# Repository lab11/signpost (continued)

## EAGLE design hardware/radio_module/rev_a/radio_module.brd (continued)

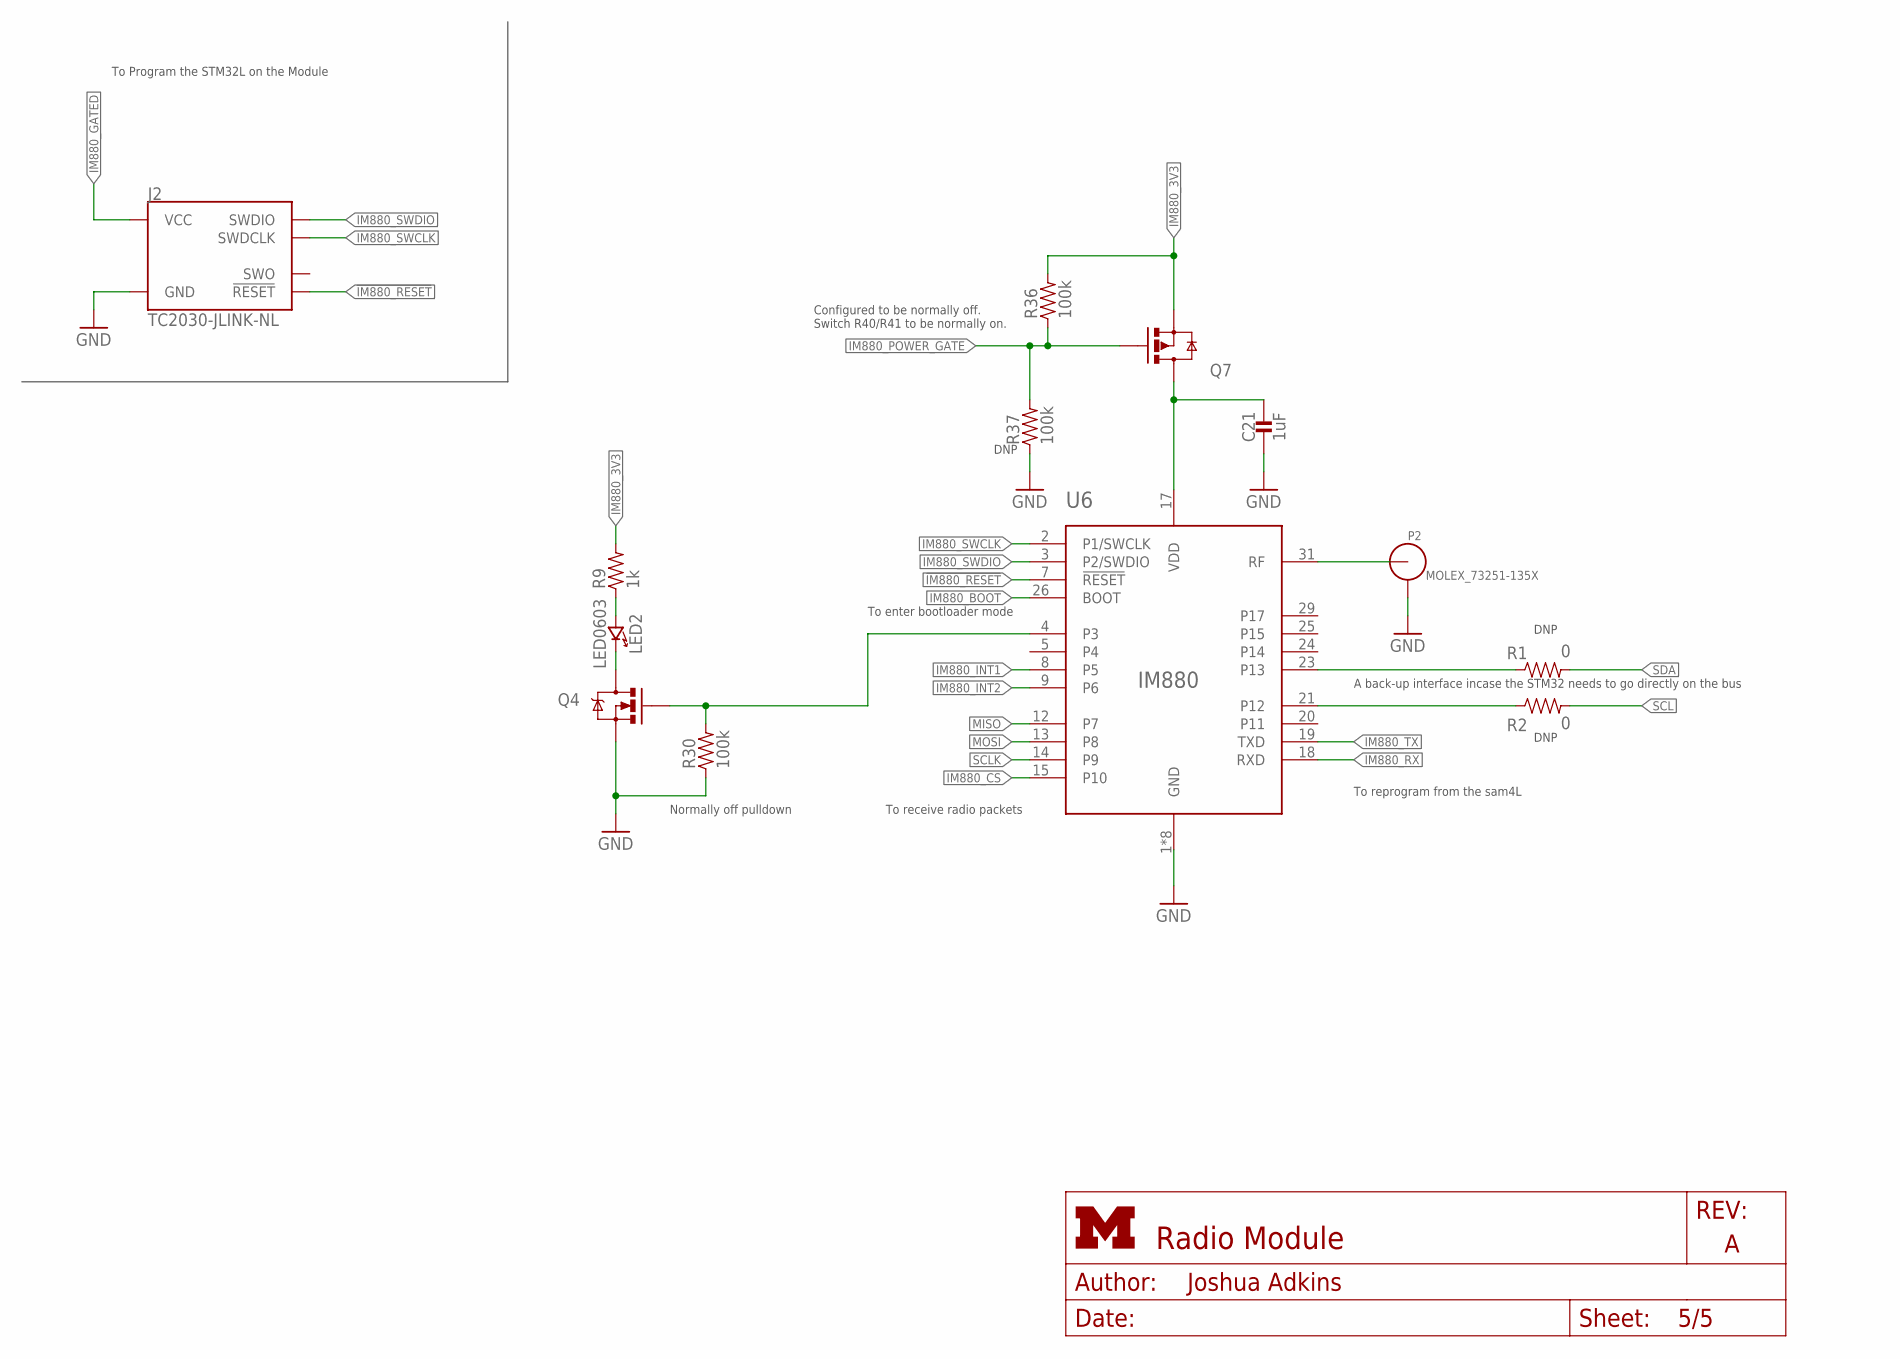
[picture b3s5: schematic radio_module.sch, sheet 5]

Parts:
C21: 1uF; 0402_CAP
J2: TC2030-JLINK-NL; TC2030-IDC-NL
LED2: LED0603; LED-0603
P2: MOLEX_73251-135X; SMA-J/PCB
Q4: MOSFET-NCHANNELXFDN-3; XFDFN-3
Q7: SI223DDS; SOT23-3
R1, R2: 0; 0402_RES
R9: 1k; 0402_RES
R30, R36, R37: 100k; 0402_RES
U6: IM880_MODULE

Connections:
!IM880_RESET: J2.3 (!RESET), U6.7 (!RESET); also elsewhere on the board
GND: C21.2, J2.5 (GND), P2.2, P2.3, P2.4, P2.5, Q4.S, R30.1, R37.1, U6.1 (GND), U6.6 (GND), U6.11 (GND), U6.16 (GND), U6.22 (GND), U6.27 (GND), U6.30 (GND), U6.32 (GND); also elsewhere on the board
IM880_3V3: Q7.2 (S), R9.2, R36.2; also elsewhere on the board
IM880_BOOT: U6.26 (BOOT); also elsewhere on the board
IM880_CS: U6.15 (P10); also elsewhere on the board
IM880_GATED: C21.1, J2.1 (VCC), Q7.3 (D), U6.17 (VDD)
IM880_INT1: U6.8 (P5); also elsewhere on the board
IM880_INT2: U6.9 (P6); also elsewhere on the board
IM880_NETWORK: Q4.G, R30.2, U6.4 (P3)
IM880_POWER_GATE: Q7.1 (G), R36.1, R37.2; also elsewhere on the board
IM880_RX: U6.18 (RXD); also elsewhere on the board
IM880_SWCLK: J2.4 (SWDCLK), U6.2 (P1/SWCLK)
IM880_SWDIO: J2.2 (SWDIO), U6.3 (P2/SWDIO)
IM880_TX: U6.19 (TXD); also elsewhere on the board
MISO: U6.12 (P7); also elsewhere on the board
MOSI: U6.13 (P8); also elsewhere on the board
unnamed: P2.1 (ANT), U6.31 (RF)
unnamed: R1.1, U6.23 (P13)
unnamed: R2.1, U6.21 (P12)
unnamed: LED2.A (ANODE), R9.1
unnamed: LED2.C (CATHODE), Q4.D
SCL: R2.2; also elsewhere on the board
SCLK: U6.14 (P9); also elsewhere on the board
SDA: R1.2; also elsewhere on the board

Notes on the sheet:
To Program the STM32L on the Module
To reprogram from the sam4L
To receive radio packets
A back-up interface incase the STM32 needs to go directly on the bus
To enter bootloader mode
DNP
Configured to be normally off. Switch R40/R41 to be normally on.
Normally off pulldown

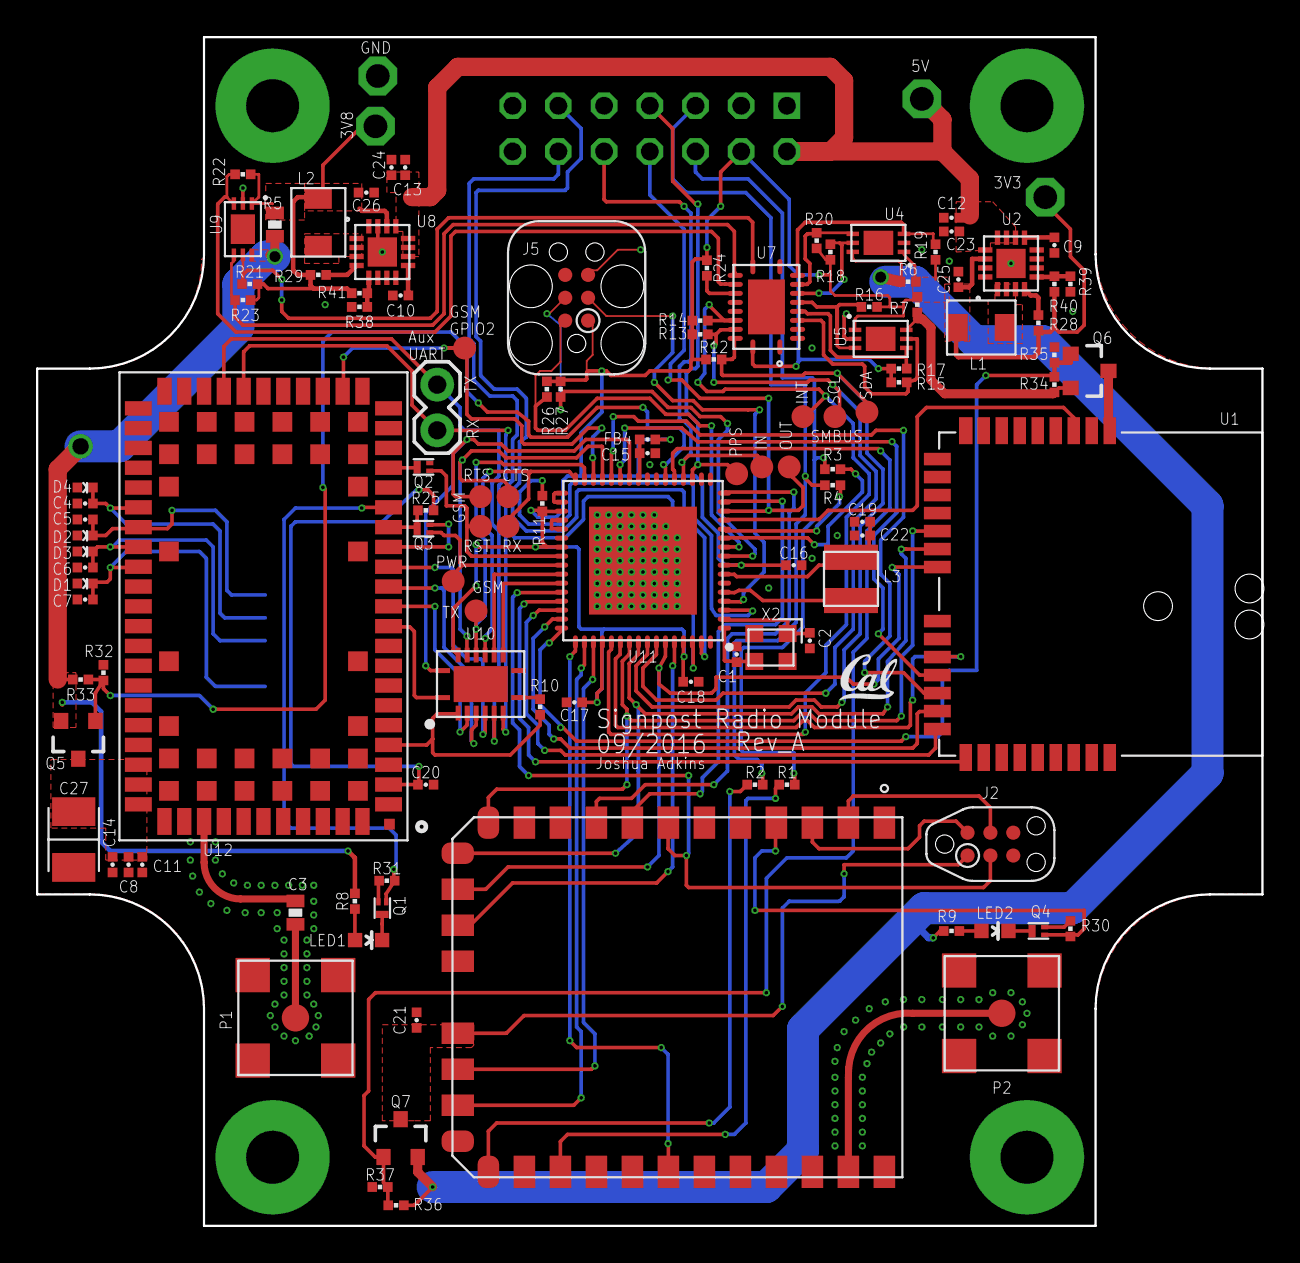
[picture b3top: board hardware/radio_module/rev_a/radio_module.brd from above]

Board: 4 copper layers, 68.1 x 66.0 mm, 122 parts (1 on the bottom side), 108 nets.

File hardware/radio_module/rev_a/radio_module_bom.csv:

# Bill of Materials
# Converted from radio_module_bom.xlsx
# Generated by bom_to_text.py

Part,Value,Device,Package,Description,DIGIKEY
C1,8pF,CAPACITOR0402_CAP,0402_CAP,0402 Capacitor,490-5867-1-ND
C2,8pF,CAPACITOR0402_CAP,0402_CAP,0402 Capacitor,490-5867-1-ND
C3,33pF,CAPACITOR0603_CAP,0603_CAP,0402 Capacitor,490-6241-1-ND
C4,47pF,CAPACITOR0402_CAP,0402_CAP,0402 Capacitor,491-6241-1-ND
C5,47pF,CAPACITOR0402_CAP,0402_CAP,0402 Capacitor,492-6241-1-ND
C6,47pF,CAPACITOR0402_CAP,0402_CAP,0402 Capacitor,493-6241-1-ND
C7,47pF,CAPACITOR0402_CAP,0402_CAP,0402 Capacitor,494-6241-1-ND
C8,56pF,CAPACITOR0402_CAP,0402_CAP,0402 Capacitor,490-1288-1-ND
C9,3.3nF,CAPACITOR0402_CAP,0402_CAP,0402 Capacitor,490-3248-1-ND
C10,3.3nF,CAPACITOR0402_CAP,0402_CAP,0402 Capacitor,491-3248-1-ND
C11,10nF,CAPACITOR0402_CAP,0402_CAP,0402 Capacitor,490-4516-1-ND
C12,0.1uF,CAPACITOR0402_CAP,0402_CAP,0402 Capacitor,490-6328-1-ND
C13,0.1uF,CAPACITOR0402_CAP,0402_CAP,0402 Capacitor,491-6328-1-ND
C14,100nF,CAPACITOR0402_CAP,0402_CAP,0402 Capacitor,492-6328-1-ND
C15,100nF,CAPACITOR0402_CAP,0402_CAP,0402 Capacitor,493-6328-1-ND
C16,100nF,CAPACITOR0402_CAP,0402_CAP,0402 Capacitor,494-6328-1-ND
C17,100nF,CAPACITOR0402_CAP,0402_CAP,0402 Capacitor,495-6328-1-ND
C18,100nF,CAPACITOR0402_CAP,0402_CAP,0402 Capacitor,496-6328-1-ND
C19,100nF,CAPACITOR0402_CAP,0402_CAP,0402 Capacitor,497-6328-1-ND
C20,100nF,CAPACITOR0402_CAP,0402_CAP,0402 Capacitor,498-6328-1-ND
C21,1uF,CAPACITOR0402_CAP,0402_CAP,0402 Capacitor,490-1320-1-ND
C22,4.7uF,CAPACITOR0402_CAP,0402_CAP,0402 Capacitor,490-5915-1-ND
C23,10uF,CAPACITOR0402_CAP,0402_CAP,0402 Capacitor,311-1729-1-ND
C24,10uF,CAPACITOR0402_CAP,0402_CAP,0402 Capacitor,312-1729-1-ND
C25,22uF,CAPACITOR0402_CAP,0402_CAP,0402 Capacitor,1276-6834-1-ND
C26,22uF,CAPACITOR0402_CAP,0402_CAP,0402 Capacitor,1277-6834-1-ND
C27,220uF,CAPACITOR1210_CAP,1210_CAP,0402 Capacitor,1276-3375-1-ND
D1,,DIODE_ZENER,0402_DIODE,,PESD0402-140CT-ND
D2,,DIODE_ZENER,0402_DIODE,,PESD0402-140CT-ND
D3,,DIODE_ZENER,0402_DIODE,,PESD0402-140CT-ND
D4,,DIODE_ZENER,0402_DIODE,,PESD0402-140CT-ND
FB4,1.5k,FERRITE_BEAD0402,0402_CAP,,490-5216-1-ND
J1,MODULE_GENERIC,MODULE_GENERIC,MODULE_GENERIC,Module header and PCB  guildes for signposts,S9170-ND
J4,NANO_SIM,NANO_SIM,WURTH_NANO_SIM,WURTH Nano SIM Connector,732-5954-1-ND
JP1,,M02PTH,1X02,Header 2,3M9447-ND
L1,2.2uH,INDUCTORIHL,IHL-1212BZ-11,A very specific inductor,541-1322-1-ND
L2,2.2uH,INDUCTORIHL,IHL-1212BZ-11,A very specific inductor,541-1322-1-ND
L3,22uH,LHQ3NP,1212,LHQ3NP Inductor,490-5350-1-ND
LED1,LED0603,LED0603,LED-0603,LED,511-1578-1-ND
LED2,LED0603,LED0603,LED-0603,LED,512-1578-1-ND
P1,MOLEX_73251-135X,MOLEX_73251-135X,SMA-J/PCB,SMA JACK SMT 50 OHM,WM9357-ND
P2,MOLEX_73251-135X,MOLEX_73251-135X,SMA-J/PCB,SMA JACK SMT 50 OHM,WM9357-ND
Q1,MOSFET-NCHANNELXFDN-3,MOSFET-NCHANNELXFDN-3,XFDFN-3,Generic NMOS footprint,DMN2400UFB4-7DICT-ND
Q2,MOSFET-NCHANNELXFDN-3,MOSFET-NCHANNELXFDN-3,XFDFN-3,Generic NMOS footprint,DMN2400UFB4-7DICT-ND
Q3,MOSFET-NCHANNELXFDN-3,MOSFET-NCHANNELXFDN-3,XFDFN-3,Generic NMOS footprint,DMN2400UFB4-7DICT-ND
Q4,MOSFET-NCHANNELXFDN-3,MOSFET-NCHANNELXFDN-3,XFDFN-3,Generic NMOS footprint,DMN2400UFB4-7DICT-ND
Q5,SI223DDS,SI223DDS,SOT23-3,6A SOT-23 P Fet,SI2333DDS-T1-GE3CT-ND
Q6,SI223DDS,SI223DDS,SOT23-3,6A SOT-23 P Fet,SI2333DDS-T1-GE3CT-ND
Q7,SI223DDS,SI223DDS,SOT23-3,6A SOT-23 P Fet,SI2333DDS-T1-GE3CT-ND
R1,0,RESISTOR0402_RES,0402_RES,Resistor,311-0.0JRCT-ND
R2,0,RESISTOR0402_RES,0402_RES,Resistor,312-0.0JRCT-ND
R3,0,RESISTOR0402_RES,0402_RES,Resistor,313-0.0JRCT-ND
R4,0,RESISTOR0402_RES,0402_RES,Resistor,314-0.0JRCT-ND
R5,0.015,RESISTOR0603_RES,0603-RES,Resistor,408-1406-1-ND
R6,0.43,RESISTOR0402_RES,0402_RES,Resistor,P.43AKCT-ND
R7,3.32,RESISTOR0402_RES,0402_RES,Resistor,541-3.32LLCT-ND
R8,1k,RESISTOR0402_RES,0402_RES,Resistor,311-1.0KJRCT-ND
R9,1k,RESISTOR0402_RES,0402_RES,Resistor,312-1.0KJRCT-ND
R10,10k,RESISTOR0402_RES,0402_RES,Resistor,311-10KJRCT-ND
R11,10k,RESISTOR0402_RES,0402_RES,Resistor,312-10KJRCT-ND
R12,10k,RESISTOR0402_RES,0402_RES,Resistor,313-10KJRCT-ND
R13,10k,RESISTOR0402_RES,0402_RES,Resistor,314-10KJRCT-ND
R14,10k,RESISTOR0402_RES,0402_RES,Resistor,315-10KJRCT-ND
R15,10k,RESISTOR0402_RES,0402_RES,Resistor,316-10KJRCT-ND
R16,10k,RESISTOR0402_RES,0402_RES,Resistor,317-10KJRCT-ND
R17,10k,RESISTOR0402_RES,0402_RES,Resistor,318-10KJRCT-ND
R18,10k,RESISTOR0402_RES,0402_RES,Resistor,319-10KJRCT-ND
R19,10k,RESISTOR0402_RES,0402_RES,Resistor,320-10KJRCT-ND
R20,10k,RESISTOR0402_RES,0402_RES,Resistor,321-10KJRCT-ND
R21,10k,RESISTOR0402_RES,0402_RES,Resistor,322-10KJRCT-ND
R22,10k,RESISTOR0402_RES,0402_RES,Resistor,323-10KJRCT-ND
R23,10k,RESISTOR0402_RES,0402_RES,Resistor,324-10KJRCT-ND
R24,10k,RESISTOR0402_RES,0402_RES,Resistor,325-10KJRCT-ND
R25,100k,RESISTOR0402_RES,0402_RES,Resistor,311-100KLRCT-ND
R26,100k,RESISTOR0402_RES,0402_RES,Resistor,312-100KLRCT-ND
R27,100k,RESISTOR0402_RES,0402_RES,Resistor,313-100KLRCT-ND
R28,100k,RESISTOR0402_RES,0402_RES,Resistor,314-100KLRCT-ND
R29,100k,RESISTOR0402_RES,0402_RES,Resistor,315-100KLRCT-ND
R30,100k,RESISTOR0402_RES,0402_RES,Resistor,316-100KLRCT-ND
R31,100k,RESISTOR0402_RES,0402_RES,Resistor,317-100KLRCT-ND
R32,100k,RESISTOR0402_RES,0402_RES,Resistor,318-100KLRCT-ND
R33,100k,RESISTOR0402_RES,0402_RES,Resistor,319-100KLRCT-ND
R34,100k,RESISTOR0402_RES,0402_RES,Resistor,320-100KLRCT-ND
R35,100k,RESISTOR0402_RES,0402_RES,Resistor,321-100KLRCT-ND
R36,100k,RESISTOR0402_RES,0402_RES,Resistor,322-100KLRCT-ND
R37,100k,RESISTOR0402_RES,0402_RES,Resistor,323-100KLRCT-ND
R38,200k,RESISTOR0402_RES,0402_RES,Resistor,P200KLCT-ND
R39,240k,RESISTOR0402_RES,0402_RES,Resistor,YAG3291CT-ND
R40,750k,RESISTOR0402_RES,0402_RES,Resistor,YAG3228CT-ND
R41,750k,RESISTOR0402_RES,0402_RES,Resistor,YAG3228CT-ND
U1,NUCLEUM,NUCLEUM,NUCLEUM,Nucleum sensorboard prototyping module.,
U2,TLV62130,TLV62130,TQFN-16/3MM,"High Efficient 3A switching step-down regulator. 1V-5V out, 4V-17V in.",296-35978-1-ND
U4,LTC2941,LTC2941,DFN-6-2MMX3MM,I2C Battery Gas Gauge,LTC2941IDCB#TRMPBFCT-ND
U5,LTC2941,LTC2941,DFN-6-2MMX3MM,I2C Battery Gas Gauge,LTC2941IDCB#TRMPBFCT-ND
U6,IM880_MODULE,IM880_MODULE,IM880_MODULE,Lora Radio module by IMST,
U7,PCA9544AQFN-N20,PCA9544AQFN-N20,QFN-N20,1-4 I2C/SMBUS Multiplexer with interrupt for power supply coulomb counters,296-20960-1-ND
U8,TLV62130,TLV62130,TQFN-16/3MM,"High Efficient 3A switching step-down regulator. 1V-5V out, 4V-17V in.",296-35978-1-ND
U9,LTC2941,LTC2941,DFN-6-2MMX3MM,I2C Battery Gas Gauge,LTC2941IDCB#TRMPBFCT-ND
U10,TXB0106,TXB0106,R-PVQFN-N16,6 channel level translator,296-23868-2-ND
U11,SAM4LC8BA,SAM4LC8BA,QFN-64-9MM,SAM4L Microcontroller. 64QFN Package. 512 Flash.,ATSAM4LC8BA-MURDKR-ND
U12,UBLOX_SARA_G350,UBLOX_SARA_G350,UBLOX_SARA_G3,Sara G350 2.5G Radio Module,
X2,16 MHz,FH1600015,FHXXX,Pericom Type FH 16 MHz 2.5 x 2.0 mm,FH1600015CT-ND

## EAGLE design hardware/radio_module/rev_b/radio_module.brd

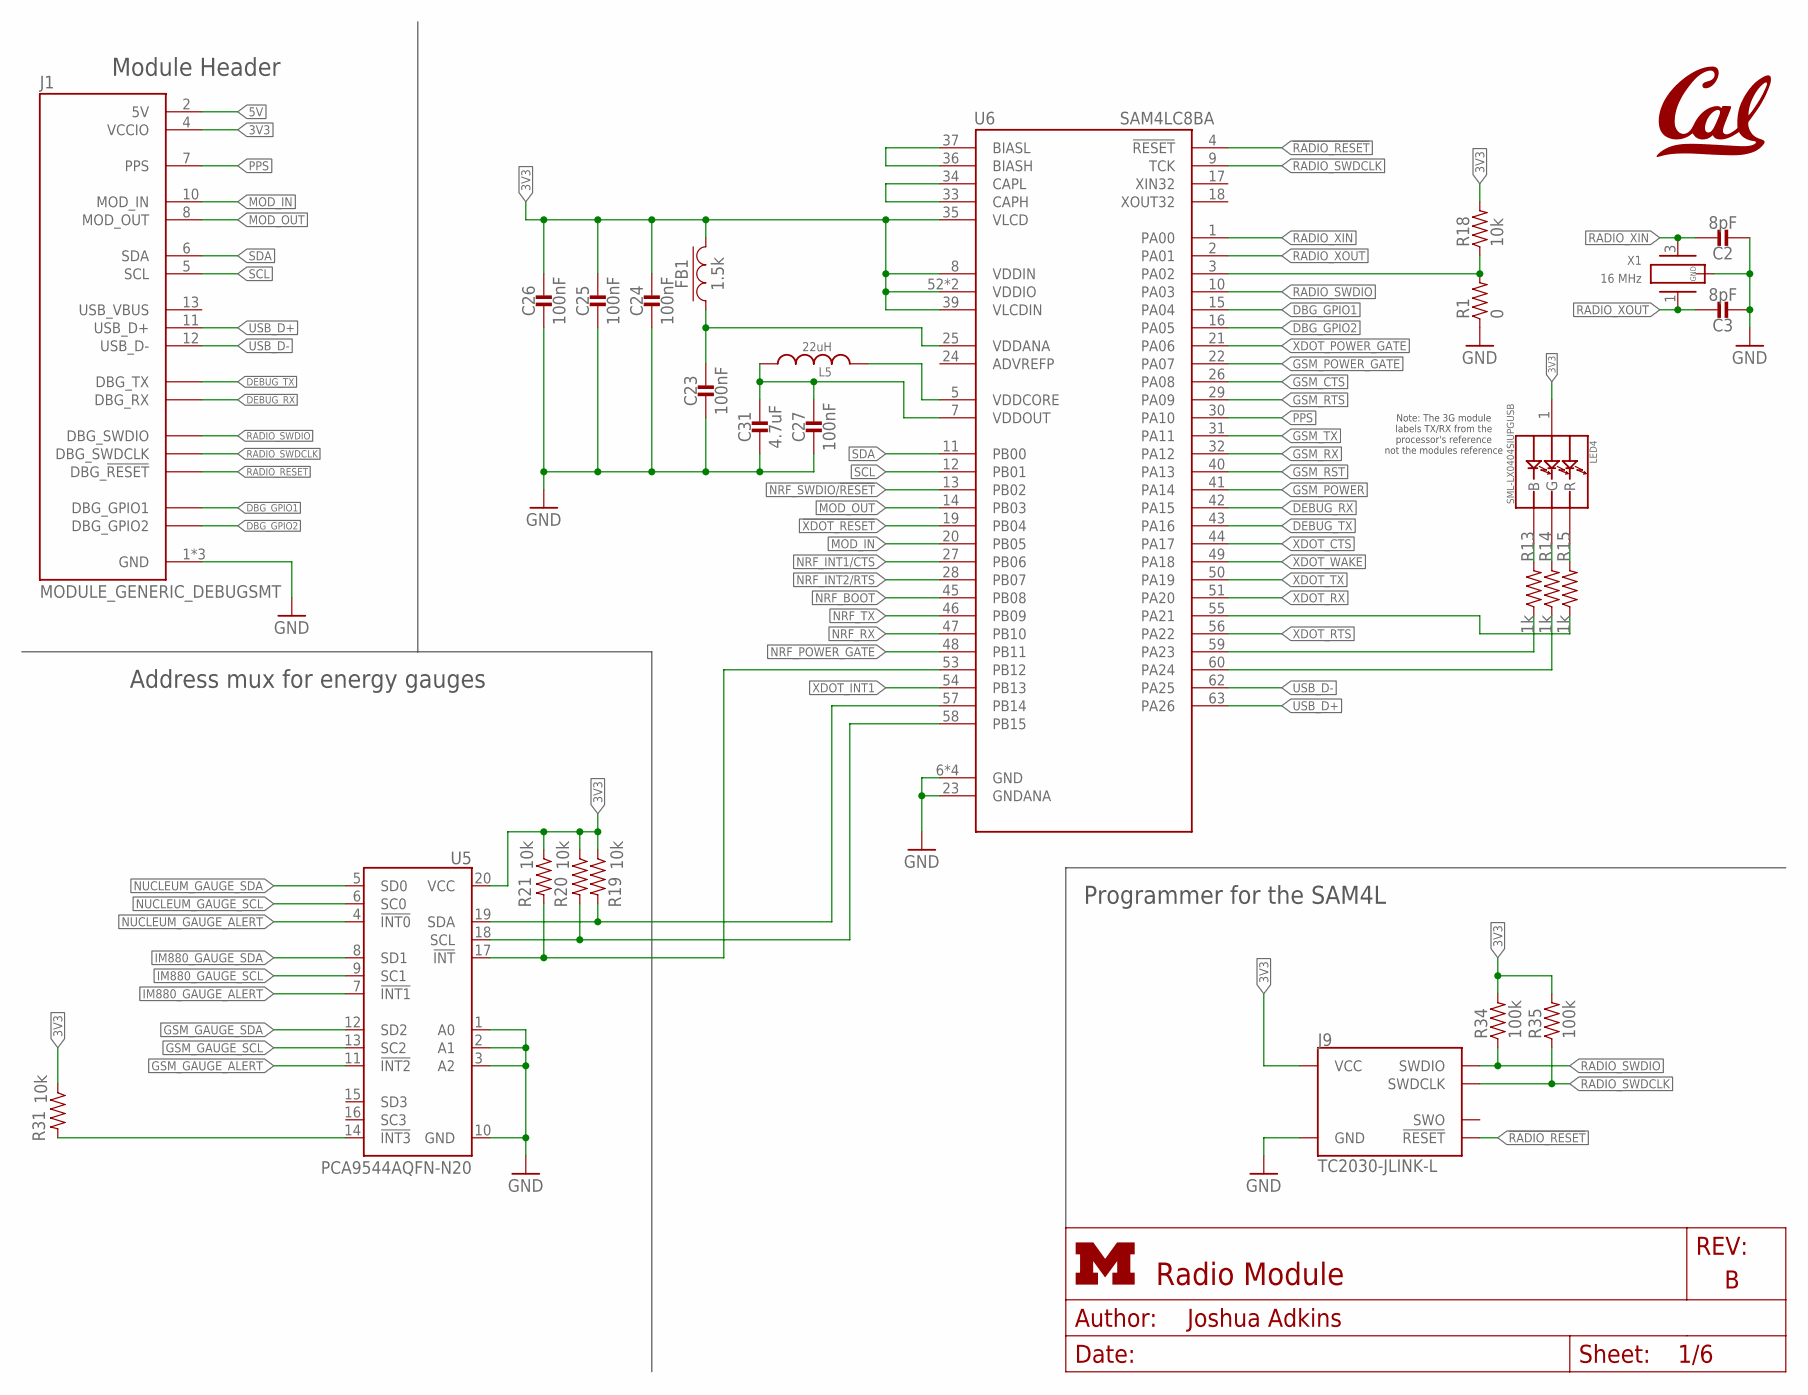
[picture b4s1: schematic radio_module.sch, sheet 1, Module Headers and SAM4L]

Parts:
C2, C3: 8pF; 0402_CAP; DIGIKEY 490-8230-1-ND
C23, C24, C25, C26, C27: 100nF; 0402_CAP; DIGIKEY 490-10777-1-ND
C31: 4.7uF; 0402_CAP; DIGIKEY 490-13252-1-ND
FB1: 1.5k; 0402_CAP; DIGIKEY 490-5216-1-ND
J1: MODULE_GENERIC_DEBUGSMT; MODULE_GENERIC_DEBUG_SMT
J9: TC2030-JLINK-L; TC2030-IDC
L5: 22uH; 1212
LED4: SML-LX0404SIUPGUSB; 1MM_SQ_4PAD
R1: 0; 0402_RES; DIGIKEY 311-0.0JRCT-ND
R13, R14, R15: 1k; 0402_RES; DIGIKEY 311-1.0KJRCT-ND
R18, R19, R20, R21, R31: 10k; 0402_RES; DIGIKEY 311-10KJRCT-ND
R34, R35: 100k; 0402_RES; DIGIKEY 311-100KLRCT-ND
U5: PCA9544AQFN-N20; QFN-N20
U6: SAM4LC8BA; QFN-64-9MM; DIGIKEY ATSAM4LC8BA-MU
U$1: UCB_CAL100MIL; UCB_CAL_100MIL
X1: 16 MHz; FHXXX

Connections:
3V3: C24.1, C25.1, C26.1, FB1.2, J1.4 (VCCIO), J9.1 (VCC), LED4.1 (VDD), R18.2, R19.1, R20.1, R21.1, R31.1, R34.2, R35.2, U5.20 (VCC), U6.8 (VDDIN), U6.35 (VLCD), U6.39 (VLCDIN), U6.52 (VDDIO), U6.61 (VDDIO); also elsewhere on the board
5V: J1.2 (5V); also elsewhere on the board
!RADIO_RESET: J1.20 (DBG_!RESET), J9.3 (!RESET), U6.4 (!RESET)
!XDOT_RESET: U6.19 (PB04); also elsewhere on the board
CONTROLLER_BUCK/LDO_N: R1.2, R18.1, U6.3 (PA02)
DBG_GPIO1: J1.16 (DBG_GPIO1), U6.15 (PA04)
DBG_GPIO2: J1.19 (DBG_GPIO2), U6.16 (PA05)
DEBUG_RX: J1.18 (DBG_RX), U6.42 (PA15)
DEBUG_TX: J1.17 (DBG_TX), U6.43 (PA16)
GND: C2.2, C3.2, C23.2, C24.2, C25.2, C26.2, C27.2, C31.2, J1.1 (GND), J1.14 (GND), J1.15 (GND), J9.5 (GND), R1.1, U5.1 (A0), U5.2 (A1), U5.3 (A2), U5.10 (GND), U6.6 (GND), U6.23 (GNDANA), U6.38 (GND), U6.64 (GND), U6.GND, X1.2 (GND), X1.4 (GND); also elsewhere on the board
GSM_CTS: U6.26 (PA08); also elsewhere on the board
GSM_GAUGE_ALERT: U5.11 (!INT2); also elsewhere on the board
GSM_GAUGE_SCL: U5.13 (SC2); also elsewhere on the board
GSM_GAUGE_SDA: U5.12 (SD2); also elsewhere on the board
GSM_POWER: U6.41 (PA14); also elsewhere on the board
GSM_POWER_GATE: U6.22 (PA07); also elsewhere on the board
GSM_RST: U6.40 (PA13); also elsewhere on the board
GSM_RTS: U6.29 (PA09); also elsewhere on the board
GSM_RX: U6.32 (PA12); also elsewhere on the board
GSM_TX: U6.31 (PA11); also elsewhere on the board
IM880_GAUGE_ALERT: U5.7 (!INT1); also elsewhere on the board
IM880_GAUGE_SCL: U5.9 (SC1); also elsewhere on the board
IM880_GAUGE_SDA: U5.8 (SD1); also elsewhere on the board
MOD_IN: J1.10 (MOD_IN), U6.20 (PB05)
MOD_OUT: J1.8 (MOD_OUT), U6.14 (PB03)
unnamed: R21.2, U5.17 (!INT), U6.53 (PB12)
unnamed: R31.2, U5.14 (!INT3)
unnamed: R13.1, U6.59 (PA23)
unnamed: LED4.3 (B), R13.2
unnamed: LED4.4 (G), R14.2
unnamed: LED4.2 (R), R15.2
unnamed: R14.1, U6.60 (PA24)
unnamed: R15.1, U6.55 (PA21)
unnamed: C23.1, FB1.1, U6.25 (VDDANA)
unnamed: C27.1, C31.1, L5.P$1 (1), U6.7 (VDDOUT)
unnamed: L5.P$2 (2), U6.5 (VDDCORE)
unnamed: U6.36 (BIASH), U6.37 (BIASL)
unnamed: U6.33 (CAPH), U6.34 (CAPL)
NRF_BOOT: U6.45 (PB08); also elsewhere on the board
NRF_INT1/CTS: U6.27 (PB06); also elsewhere on the board
NRF_INT2/RTS: U6.28 (PB07); also elsewhere on the board
NRF_POWER_GATE: U6.48 (PB11); also elsewhere on the board
NRF_RX: U6.47 (PB10); also elsewhere on the board
NRF_SWDIO/!RESET: U6.13 (PB02); also elsewhere on the board
NRF_TX: U6.46 (PB09); also elsewhere on the board
NUCLEUM_GAUGE_ALERT: U5.4 (!INT0); also elsewhere on the board
NUCLEUM_GAUGE_SCL: U5.6 (SC0); also elsewhere on the board
NUCLEUM_GAUGE_SDA: U5.5 (SD0); also elsewhere on the board
PPS: J1.7 (PPS), U6.30 (PA10)
RADIO_SWDCLK: J1.21 (DBG_SWDCLK), J9.4 (SWDCLK), R35.1, U6.9 (TCK)
RADIO_SWDIO: J1.22 (DBG_SWDIO), J9.2 (SWDIO), R34.1, U6.10 (PA03)
RADIO_XIN: C2.1, U6.1 (PA00), X1.3 (2)
RADIO_XOUT: C3.1, U6.2 (PA01), X1.1
SCL: J1.5 (SCL), U6.12 (PB01)
SCL_INTERNAL: R20.2, U5.18 (SCL), U6.58 (PB15)
SDA: J1.6 (SDA), U6.11 (PB00)
SDA_INTERNAL: R19.2, U5.19 (SDA), U6.57 (PB14)
USB_D+: J1.11 (USB_D+), U6.63 (PA26)
USB_D-: J1.12 (USB_D-), U6.62 (PA25)
XDOT_CTS: U6.44 (PA17); also elsewhere on the board
XDOT_INT1: U6.54 (PB13); also elsewhere on the board
XDOT_POWER_GATE: U6.21 (PA06); also elsewhere on the board
XDOT_RTS: U6.56 (PA22); also elsewhere on the board
XDOT_RX: U6.51 (PA20); also elsewhere on the board
XDOT_TX: U6.50 (PA19); also elsewhere on the board
XDOT_WAKE: U6.49 (PA18); also elsewhere on the board

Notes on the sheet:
Module Header
Address mux for energy gauges
Programmer for the SAM4L
Note: The 3G module labels TX/RX from the processor's reference not the modules reference

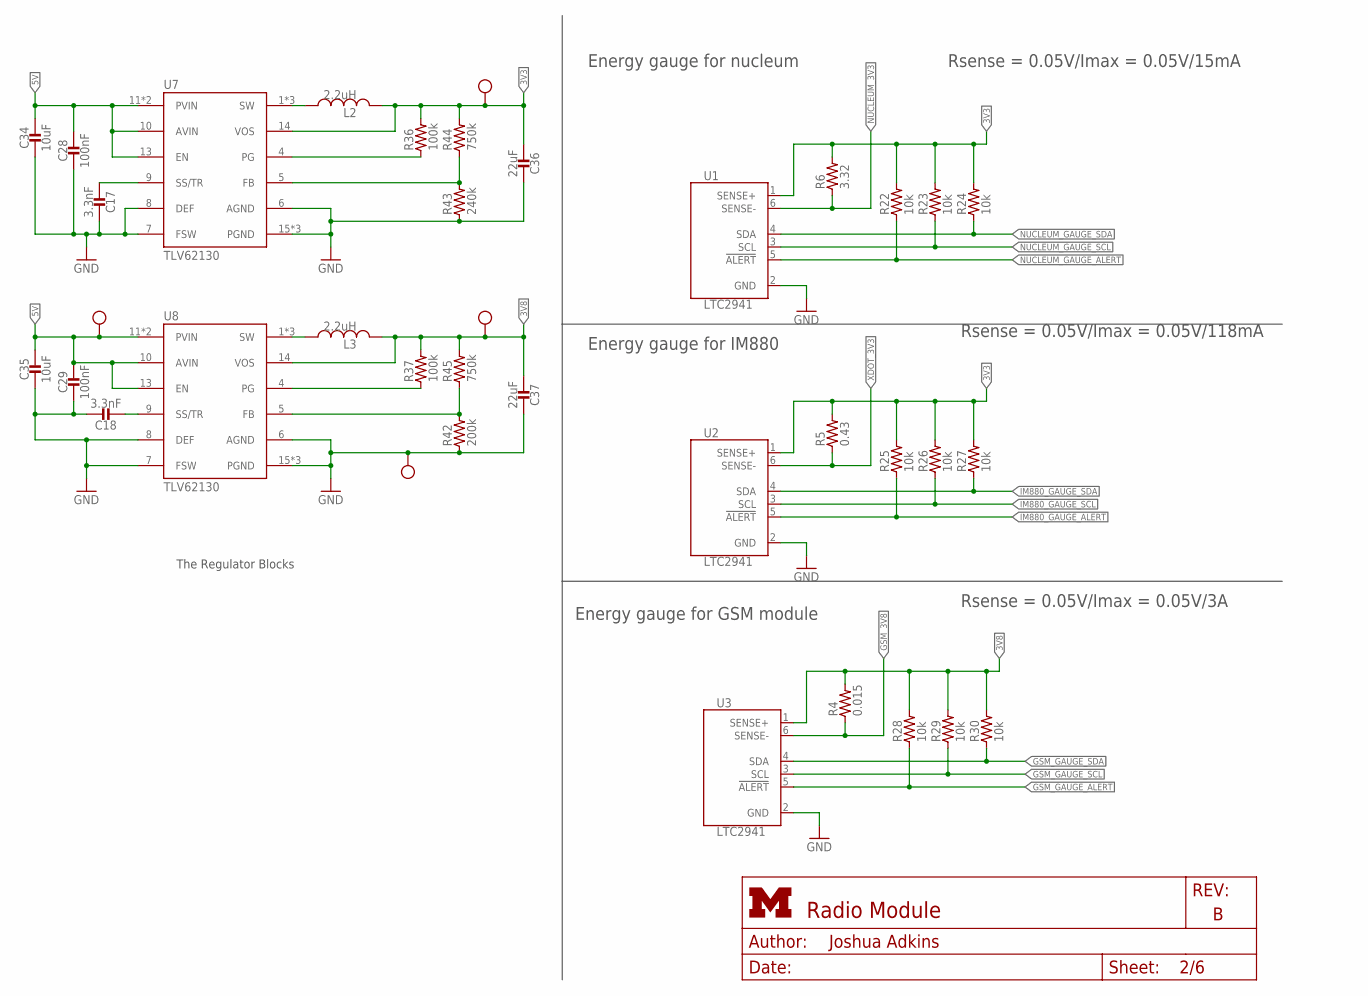
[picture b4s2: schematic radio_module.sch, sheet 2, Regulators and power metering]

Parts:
C17, C18: 3.3nF; 0402_CAP; DIGIKEY 490-3248-1-ND
C28, C29: 100nF; 0402_CAP; DIGIKEY 490-10777-1-ND
C34, C35: 10uF; 0402_CAP; DIGIKEY 490-13233-1-ND
C36, C37: 22uF; 0402_CAP; DIGIKEY 1276-6834-1-ND
L2, L3: 2.2uH; IHL-1212BZ-11
R4: 0.015; 0603-RES; DIGIKEY 408-1406-1-ND
R5: 0.43; 0402_RES; DIGIKEY P.43AKCT-ND
R6: 3.32; 0402_RES; DIGIKEY 541-3.32LLCT-ND
R22, R23, R24, R25, R26, R27, R28, R29, R30: 10k; 0402_RES; DIGIKEY 311-10KJRCT-ND
R36, R37: 100k; 0402_RES; DIGIKEY 311-100KLRCT-ND
R42: 200k; 0402_RES; DIGIKEY P200KLCT-ND
R43: 240k; 0402_RES; DIGIKEY YAG3291CT-ND
R44, R45: 750k; 0402_RES; DIGIKEY YAG3228CT-ND
TP1, TP2, TP3, TP4: TEST_POINT_0.040IN; TESTPOINT_0.040IN
U1, U2, U3: LTC2941; DFN-6-2MMX3MM
U7, U8: TLV62130; TQFN-16/3MM

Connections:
3V3: C36.2, L2.P$2 (2), R5.2, R6.2, R22.2, R23.2, R24.2, R25.2, R26.2, R27.2, R36.2, R44.2, TP1.TESTPOINT, U1.1 (SENSE+), U2.1 (SENSE+), U7.14 (VOS); also elsewhere on the board
3V8: C37.2, L3.P$2 (2), R4.2, R28.2, R29.2, R30.2, R37.2, R45.2, TP2.TESTPOINT, U3.1 (SENSE+), U8.14 (VOS)
3V8SWOUT: L3.P$1 (1), U8.1 (SW), U8.2 (SW), U8.3 (SW)
3VSWOUT: L2.P$1 (1), U7.1 (SW), U7.2 (SW), U7.3 (SW)
5V: C28.1, C29.1, C34.1, C35.1, TP4.TESTPOINT, U7.10 (AVIN), U7.11 (PVIN), U7.12 (PVIN), U7.13 (EN), U8.10 (AVIN), U8.11 (PVIN), U8.12 (PVIN), U8.13 (EN); also elsewhere on the board
GND: C17.1, C18.1, C28.2, C29.2, C34.2, C35.2, C36.1, C37.1, R42.1, R43.1, TP3.TESTPOINT, U1.2 (GND), U2.2 (GND), U3.2 (GND), U7.6 (AGND), U7.7 (FSW), U7.8 (DEF), U7.15 (PGND), U7.16 (PGND), U7.GND, U8.6 (AGND), U8.7 (FSW), U8.8 (DEF), U8.15 (PGND), U8.16 (PGND), U8.GND; also elsewhere on the board
GSM_3V8: R4.1, U3.6 (SENSE-); also elsewhere on the board
GSM_GAUGE_ALERT: R28.1, U3.5 (!ALERT); also elsewhere on the board
GSM_GAUGE_SCL: R29.1, U3.3 (SCL); also elsewhere on the board
GSM_GAUGE_SDA: R30.1, U3.4 (SDA); also elsewhere on the board
IM880_GAUGE_ALERT: R25.1, U2.5 (!ALERT); also elsewhere on the board
IM880_GAUGE_SCL: R26.1, U2.3 (SCL); also elsewhere on the board
IM880_GAUGE_SDA: R27.1, U2.4 (SDA); also elsewhere on the board
unnamed: C17.2, U7.9 (SS/TR)
unnamed: R36.1, U7.4 (PG)
unnamed: R43.2, R44.1, U7.5 (FB)
unnamed: C18.2, U8.9 (SS/TR)
unnamed: R37.1, U8.4 (PG)
unnamed: R42.2, R45.1, U8.5 (FB)
NUCLEUM_3V3: R6.1, U1.6 (SENSE-); also elsewhere on the board
NUCLEUM_GAUGE_ALERT: R22.1, U1.5 (!ALERT); also elsewhere on the board
NUCLEUM_GAUGE_SCL: R23.1, U1.3 (SCL); also elsewhere on the board
NUCLEUM_GAUGE_SDA: R24.1, U1.4 (SDA); also elsewhere on the board
XDOT_3V3: R5.1, U2.6 (SENSE-); also elsewhere on the board

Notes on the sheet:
The Regulator Blocks
Energy gauge for nucleum
Energy gauge for IM880
Energy gauge for GSM module
Rsense = 0.05V/Imax = 0.05V/15mA
Rsense = 0.05V/Imax = 0.05V/118mA
Rsense = 0.05V/Imax = 0.05V/3A

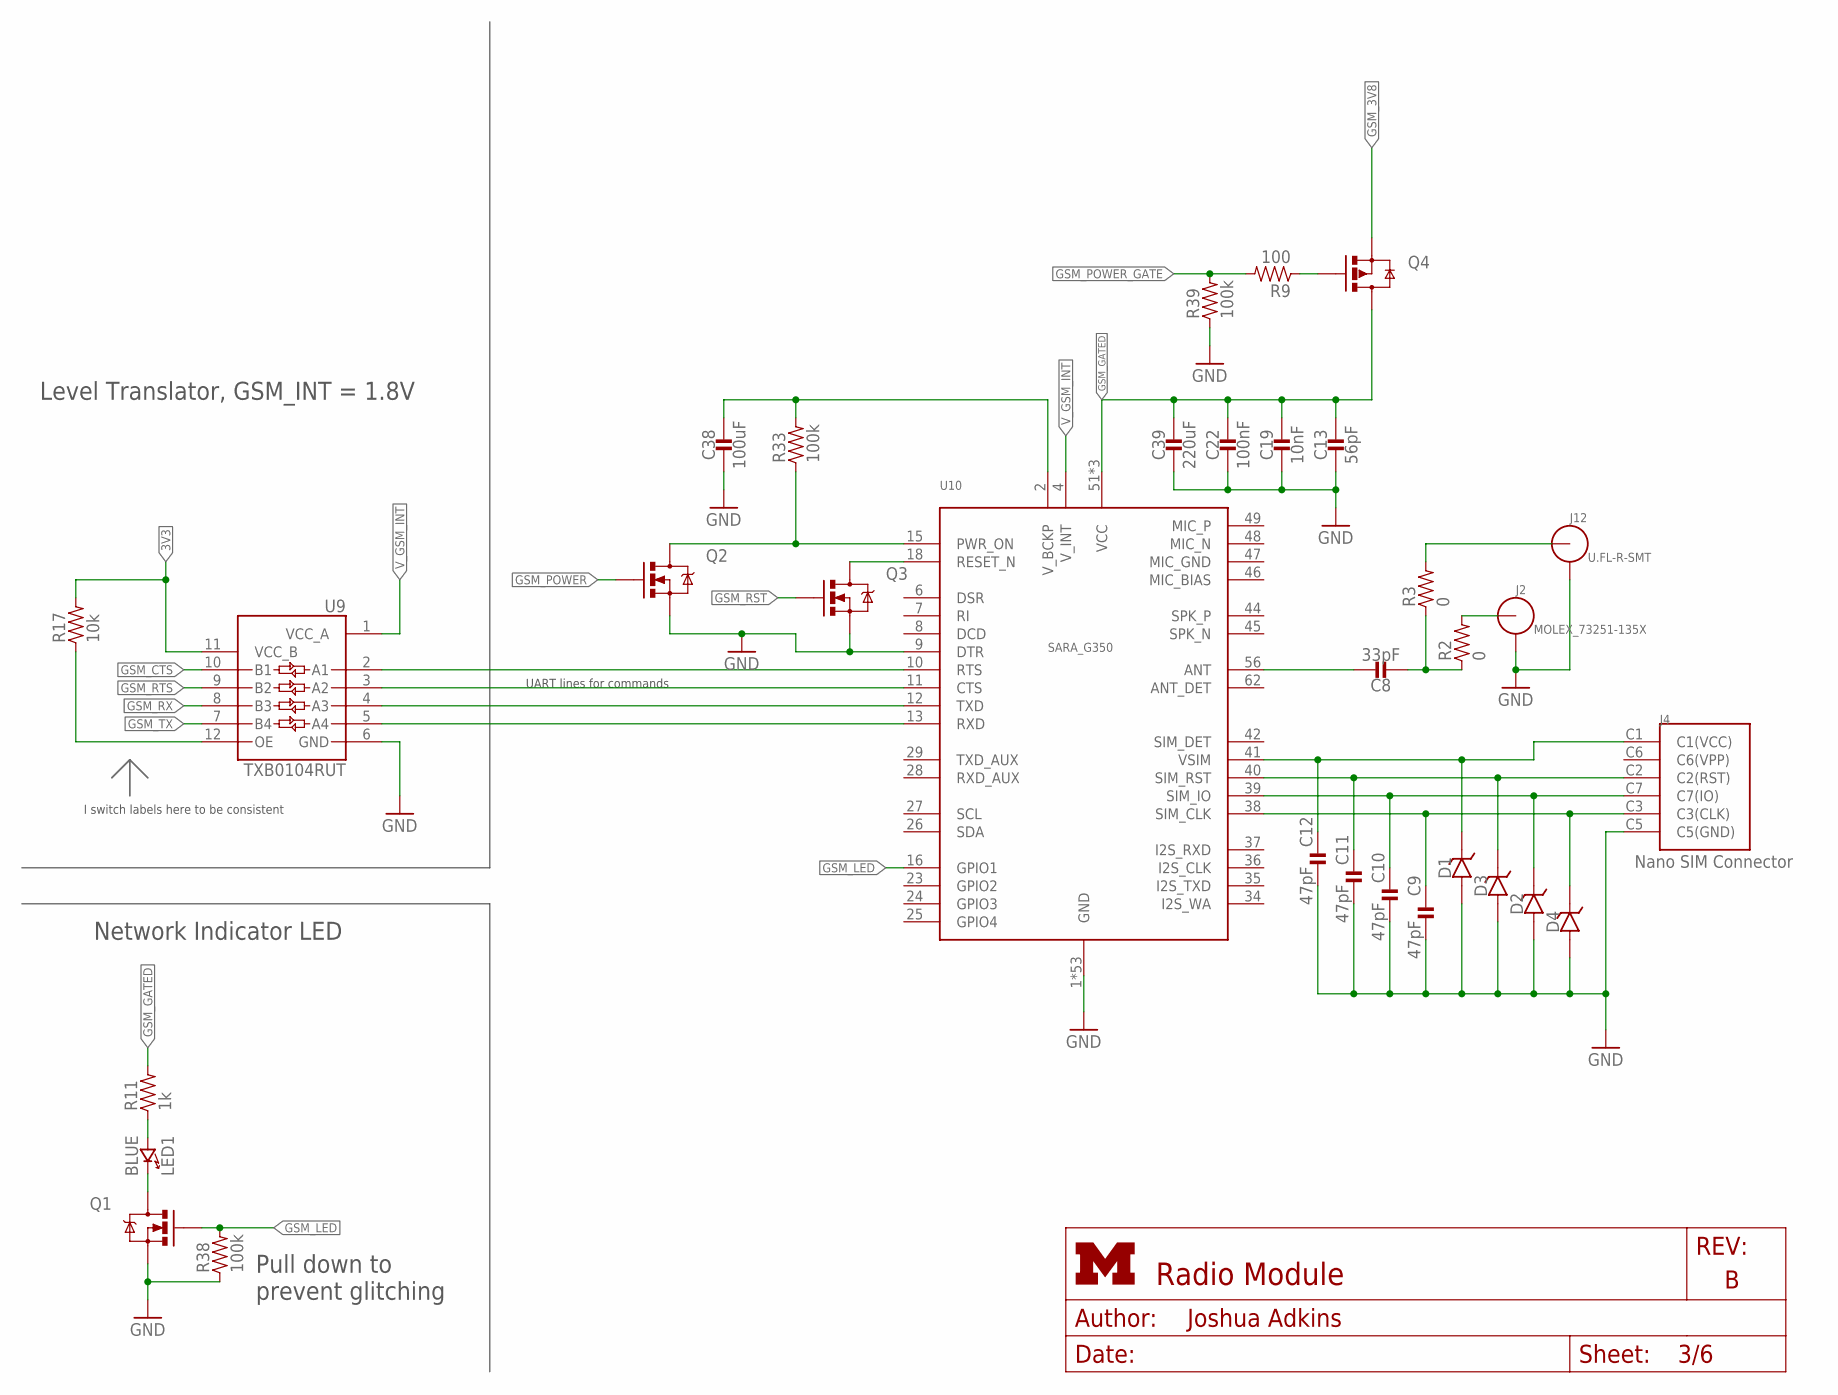
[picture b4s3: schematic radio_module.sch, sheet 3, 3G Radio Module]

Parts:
C8: 33pF; 0603_CAP; DIGIKEY 490-6241-1-ND
C9, C10, C11, C12: 47pF; 0402_CAP; DIGIKEY 490-6241-1-ND
C13: 56pF; 0402_CAP; DIGIKEY 490-1288-1-ND
C19: 10nF; 0402_CAP; DIGIKEY 490-4516-1-ND
C22: 100nF; 0402_CAP; DIGIKEY 490-10777-1-ND
C38: 100uF; 0805_CAP; DIGIKEY 490-13981-1-ND
C39: 220uF; 1210_CAP; DIGIKEY 1276-3375-1-ND
D1, D2, D3, D4: 14V; 0402_DIODE; DIGIKEY PESD0402-140CT-ND
J2: MOLEX_73251-135X; SMA-J/PCB
J4: NANO_SIM; WURTH_NANO_SIM
J12: U.FL-R-SMT; U.FL_SMT
LED1: BLUE; LED-0603; DIGIKEY 511-1578-1-ND
Q1, Q2, Q3: MOSFET-NCHANNELSMD; SOT23-3; DIGIKEY SI2333DDS-T1-GE3CT-ND
Q4: SI223DDS; SOT23-3
R2, R3: 0; 0402_RES; DIGIKEY 311-0.0JRCT-ND
R9: 100; 0402_RES; DIGIKEY 311-100LRCT-ND
R11: 1k; 0402_RES; DIGIKEY 311-1.0KJRCT-ND
R17: 10k; 0402_RES; DIGIKEY 311-10KJRCT-ND
R33, R38, R39: 100k; 0402_RES; DIGIKEY 311-100KLRCT-ND
U9: TXB0104RUT; UQFN-12
U10: UBLOX_SARA_G350; UBLOX_SARA_G3

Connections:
3V3: R17.2, U9.11 (VCC_B); also elsewhere on the board
GND: C9.2, C10.2, C11.2, C12.2, C13.2, C19.2, C22.2, C38.P$2 (2), C39.2, D1.ANODE, D2.ANODE, D3.ANODE, D4.ANODE, J2.2, J2.3, J2.4, J2.5, J4.C5 (C5(GND)), J12.GND1, J12.GND2, Q1.2 (S), Q2.2 (S), Q3.2 (S), R38.1, R39.1, U9.6 (GND), U10.1 (GND), U10.3 (GND), U10.5 (GND), U10.9 (DTR), U10.14 (GND), U10.20 (GND), U10.21 (GND), U10.22 (GND), U10.30 (GND), U10.32 (GND), U10.33 (GND), U10.43 (GND), U10.50 (GND), U10.54 (GND), U10.55 (GND), U10.57 (GND), U10.58 (GND), U10.59 (GND), U10.60 (GND), U10.61 (GND), U10.63 (GND), U10.64 (GND), U10.65 (GND), U10.66 (GND), U10.67 (GND), U10.68 (GND), U10.69 (GND), U10.70 (GND), U10.71 (GND), U10.72 (GND), U10.73 (GND), U10.74 (GND), U10.75 (GND), U10.76 (GND), U10.77 (GND), U10.78 (GND), U10.79 (GND), U10.80 (GND), U10.81 (GND), U10.82 (GND), U10.83 (GND), U10.84 (GND), U10.85 (GND), U10.86 (GND), U10.87 (GND), U10.88 (GND), U10.89 (GND), U10.90 (GND), U10.91 (GND), U10.92 (GND), U10.93 (GND), U10.94 (GND), U10.95 (GND), U10.96 (GND); also elsewhere on the board
GSM_3V8: Q4.2 (S); also elsewhere on the board
GSM_CTS: U9.10 (B1); also elsewhere on the board
GSM_GATED: C13.1, C19.1, C22.1, C39.1, Q4.3 (D), R11.2, U10.51 (VCC), U10.52 (VCC), U10.53 (VCC)
GSM_LED: Q1.1 (G), R38.2, U10.16 (GPIO1)
GSM_POWER: Q2.1 (G); also elsewhere on the board
GSM_POWER_GATE: R9.2, R39.2; also elsewhere on the board
GSM_RST: Q3.1 (G); also elsewhere on the board
GSM_RTS: U9.9 (B2); also elsewhere on the board
GSM_RX: U9.8 (B3); also elsewhere on the board
GSM_TX: U9.7 (B4); also elsewhere on the board
unnamed: C12.1, D1.CATHODE, J4.C1 (C1(VCC)), U10.41 (VSIM)
unnamed: C11.1, D3.CATHODE, J4.C2 (C2(RST)), U10.40 (SIM_RST)
unnamed: C10.1, D2.CATHODE, J4.C7 (C7(IO)), U10.39 (SIM_IO)
unnamed: C9.1, D4.CATHODE, J4.C3 (C3(CLK)), U10.38 (SIM_CLK)
unnamed: R17.1, U9.12 (OE)
unnamed: C8.1, U10.56 (ANT)
unnamed: J12.SIG (ANT), R3.2
unnamed: LED1.A (ANODE), R11.1
unnamed: U9.4 (A3), U10.12 (TXD)
unnamed: U9.5 (A4), U10.13 (RXD)
unnamed: LED1.C (CATHODE), Q1.3 (D)
unnamed: Q3.3 (D), U10.18 (RESET_N)
unnamed: C38.P$1 (1), R33.2, U10.2 (V_BCKP)
unnamed: Q2.3 (D), R33.1, U10.15 (PWR_ON)
unnamed: U9.3 (A2), U10.11 (CTS)
unnamed: U9.2 (A1), U10.10 (RTS)
unnamed: C8.2, R2.1, R3.1
unnamed: J2.1 (ANT), R2.2
unnamed: Q4.1 (G), R9.1
V_GSM_INT: U9.1 (VCC_A), U10.4 (V_INT)

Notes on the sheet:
Pull down to prevent glitching
Network Indicator LED
Level Translator, GSM_INT = 1.8V
UART lines for commands
I switch labels here to be consistent
